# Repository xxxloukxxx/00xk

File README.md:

# Des keyboards qui vont presque bien :)

- [000k](https://github.com/xxxloukxxx/00xk/tree/main/000k) : Un 40%++, pas ergo, avec une ligne en plus inspiré
- [001k](https://github.com/xxxloukxxx/00xk/tree/main/001k) : Un ergo en 3x12+5, inspiré de revuing 41
- [002k](https://github.com/xxxloukxxx/00xk/tree/main/002k) : Un ergo en 3x12+6, inspiré de revuing 41 ... encore
- [003k](https://github.com/xxxloukxxx/00xk/tree/main/003k) : Un ergo en 4x12, inspiré de revuing 41 ... encore/encore
- [004k](https://github.com/xxxloukxxx/00xk/tree/main/004k) : Un ergo 52, inspiré de HillSide52

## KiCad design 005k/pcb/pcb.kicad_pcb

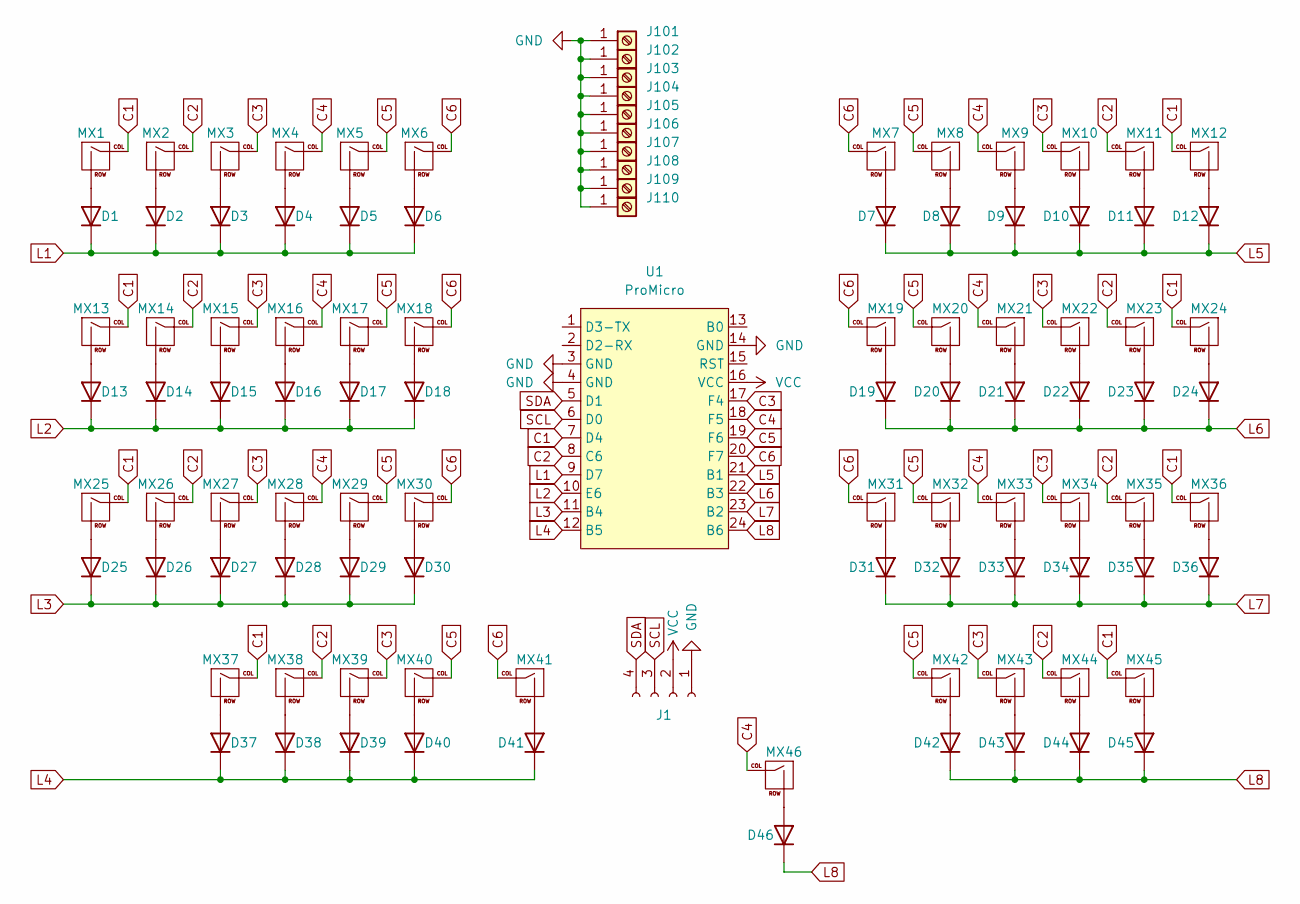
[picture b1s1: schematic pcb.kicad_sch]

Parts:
D1, D2, D3, D4, D5, D6, D7, D8, D9, D10, D11, D12, D13, D14, D15, D16, D17, D18, D19, D20, D21, D22, D23, D24, D25, D26, D27, D28, D29, D30, D31, D32, D33, D34, D35, D36, D37, D38, D39, D40, D41, D42, D43, D44, D45, D46: 1N4148; D_DO-35_SOD27_P7.62mm_Horizontal
J1: Conn_01x04_Socket; SSD1306-0.91-OLED-4pin-128x32
J101, J102, J103, J104, J105, J106, J107, J108, J109, J110: Screw_Terminal_01x01; MountingHole_2.2mm_M2
MX1, MX12, MX13, MX24, MX25, MX36, MX37, MX38, MX39, MX40, MX42: MX; MX-Alps-Hybrid-1.25U
MX2, MX3, MX4, MX5, MX6, MX7, MX8, MX9, MX10, MX11, MX14, MX15, MX16, MX17, MX18, MX19, MX20, MX21, MX22, MX23, MX26, MX27, MX28, MX29, MX30, MX31, MX32, MX33, MX34, MX35, MX43, MX44, MX45, MX46: MX; MX-Alps-Hybrid-1U
MX41: MX; MX-Alps-Hybrid-3U-ReversedStabilizers
U1: ProMicro; ProMicro_USBup

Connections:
C1: MX1.1 (COL), MX12.1 (COL), MX13.1 (COL), MX24.1 (COL), MX25.1 (COL), MX36.1 (COL), MX37.1 (COL), MX45.1 (COL), U1.7 (D4)
C2: MX2.1 (COL), MX11.1 (COL), MX14.1 (COL), MX23.1 (COL), MX26.1 (COL), MX35.1 (COL), MX38.1 (COL), MX44.1 (COL), U1.8 (C6)
C3: MX3.1 (COL), MX10.1 (COL), MX15.1 (COL), MX22.1 (COL), MX27.1 (COL), MX34.1 (COL), MX39.1 (COL), MX43.1 (COL), U1.17 (F4)
C4: MX4.1 (COL), MX9.1 (COL), MX16.1 (COL), MX21.1 (COL), MX28.1 (COL), MX33.1 (COL), MX46.1 (COL), U1.18 (F5)
C5: MX5.1 (COL), MX8.1 (COL), MX17.1 (COL), MX20.1 (COL), MX29.1 (COL), MX32.1 (COL), MX40.1 (COL), MX42.1 (COL), U1.19 (F6)
C6: MX6.1 (COL), MX7.1 (COL), MX18.1 (COL), MX19.1 (COL), MX30.1 (COL), MX31.1 (COL), MX41.1 (COL), U1.20 (F7)
GND: J1.1, J101.1, J102.1, J103.1, J104.1, J105.1, J106.1, J107.1, J108.1, J109.1, J110.1, U1.3 (GND), U1.4 (GND), U1.14 (GND)
L1: D1.1 (K), D2.1 (K), D3.1 (K), D4.1 (K), D5.1 (K), D6.1 (K), U1.9 (D7)
L2: D13.1 (K), D14.1 (K), D15.1 (K), D16.1 (K), D17.1 (K), D18.1 (K), U1.10 (E6)
L3: D25.1 (K), D26.1 (K), D27.1 (K), D28.1 (K), D29.1 (K), D30.1 (K), U1.11 (B4)
L4: D37.1 (K), D38.1 (K), D39.1 (K), D40.1 (K), D41.1 (K), U1.12 (B5)
L5: D7.1 (K), D8.1 (K), D9.1 (K), D10.1 (K), D11.1 (K), D12.1 (K), U1.21 (B1)
L6: D19.1 (K), D20.1 (K), D21.1 (K), D22.1 (K), D23.1 (K), D24.1 (K), U1.22 (B3)
L7: D31.1 (K), D32.1 (K), D33.1 (K), D34.1 (K), D35.1 (K), D36.1 (K), U1.23 (B2)
L8: D42.1 (K), D43.1 (K), D44.1 (K), D45.1 (K), D46.1 (K), U1.24 (B6)
unnamed: D1.2 (A), MX1.2 (ROW)
unnamed: D2.2 (A), MX2.2 (ROW)
unnamed: D3.2 (A), MX3.2 (ROW)
unnamed: D4.2 (A), MX4.2 (ROW)
unnamed: D5.2 (A), MX5.2 (ROW)
unnamed: D6.2 (A), MX6.2 (ROW)
unnamed: D7.2 (A), MX7.2 (ROW)
unnamed: D8.2 (A), MX8.2 (ROW)
unnamed: D9.2 (A), MX9.2 (ROW)
unnamed: D10.2 (A), MX10.2 (ROW)
unnamed: D11.2 (A), MX11.2 (ROW)
unnamed: D12.2 (A), MX12.2 (ROW)
unnamed: D13.2 (A), MX13.2 (ROW)
unnamed: D14.2 (A), MX14.2 (ROW)
unnamed: D15.2 (A), MX15.2 (ROW)
unnamed: D16.2 (A), MX16.2 (ROW)
unnamed: D17.2 (A), MX17.2 (ROW)
unnamed: D18.2 (A), MX18.2 (ROW)
unnamed: D19.2 (A), MX19.2 (ROW)
unnamed: D20.2 (A), MX20.2 (ROW)
unnamed: D21.2 (A), MX21.2 (ROW)
unnamed: D22.2 (A), MX22.2 (ROW)
unnamed: D23.2 (A), MX23.2 (ROW)
unnamed: D24.2 (A), MX24.2 (ROW)
unnamed: D25.2 (A), MX25.2 (ROW)
unnamed: D26.2 (A), MX26.2 (ROW)
unnamed: D27.2 (A), MX27.2 (ROW)
unnamed: D28.2 (A), MX28.2 (ROW)
unnamed: D29.2 (A), MX29.2 (ROW)
unnamed: D30.2 (A), MX30.2 (ROW)
unnamed: D31.2 (A), MX31.2 (ROW)
unnamed: D32.2 (A), MX32.2 (ROW)
unnamed: D33.2 (A), MX33.2 (ROW)
unnamed: D34.2 (A), MX34.2 (ROW)
unnamed: D35.2 (A), MX35.2 (ROW)
unnamed: D36.2 (A), MX36.2 (ROW)
unnamed: D37.2 (A), MX37.2 (ROW)
unnamed: D38.2 (A), MX38.2 (ROW)
unnamed: D39.2 (A), MX39.2 (ROW)
unnamed: D40.2 (A), MX40.2 (ROW)
unnamed: D41.2 (A), MX41.2 (ROW)
unnamed: D42.2 (A), MX42.2 (ROW)
unnamed: D43.2 (A), MX43.2 (ROW)
unnamed: D44.2 (A), MX44.2 (ROW)
unnamed: D45.2 (A), MX45.2 (ROW)
unnamed: D46.2 (A), MX46.2 (ROW)
SCL: J1.3, U1.6 (D0)
SDA: J1.4, U1.5 (D1)
VCC: J1.2, U1.16 (VCC)

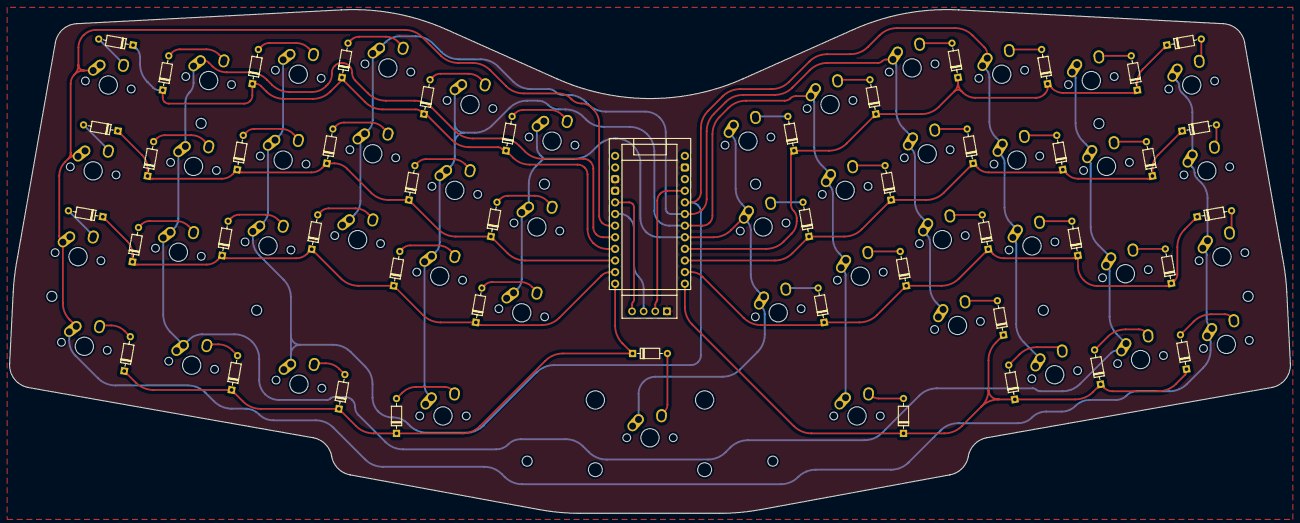
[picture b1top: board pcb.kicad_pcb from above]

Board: 2 copper layers, 279.9 x 110.1 mm, 104 parts (0 on the bottom side), 64 nets.

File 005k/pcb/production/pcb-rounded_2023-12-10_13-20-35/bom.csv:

Designator,Footprint,Quantity,Value,LCSC Part #
"D1, D10, D11, D12, D13, D14, D15, D16, D17, D18, D19, D2, D20, D21, D22, D23, D24, D25, D26, D27, D28, D29, D3, D30, D31, D32, D33, D34, D35, D36, D37, D38, D39, D4, D40, D41, D42, D43, D44, D45, D46, D47, D5, D6, D7, D8, D9",D_DO-35_SOD27_P7.62mm_Horizontal,47,1N4148,
J1,SSD1306-0.91-OLED-4pin-128x32,1,Screw_Terminal_01x04,
"MX1, MX10, MX11, MX12, MX13, MX14, MX15, MX16, MX17, MX18, MX19, MX2, MX20, MX21, MX22, MX23, MX24, MX25, MX26, MX27, MX28, MX29, MX3, MX30, MX31, MX32, MX33, MX34, MX35, MX36, MX37, MX38, MX39, MX4, MX40, MX41, MX42, MX43, MX44, MX45, MX46, MX47, MX5, MX6, MX7, MX8, MX9",MX-Alps-Hybrid-1U,47,MX,

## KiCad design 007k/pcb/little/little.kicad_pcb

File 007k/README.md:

# 007k

Pour Gigi ... Exploded One

## Little

... et pourquoi pas avec un OLED ?

## Big

à voir car pas de place pour le Promicro

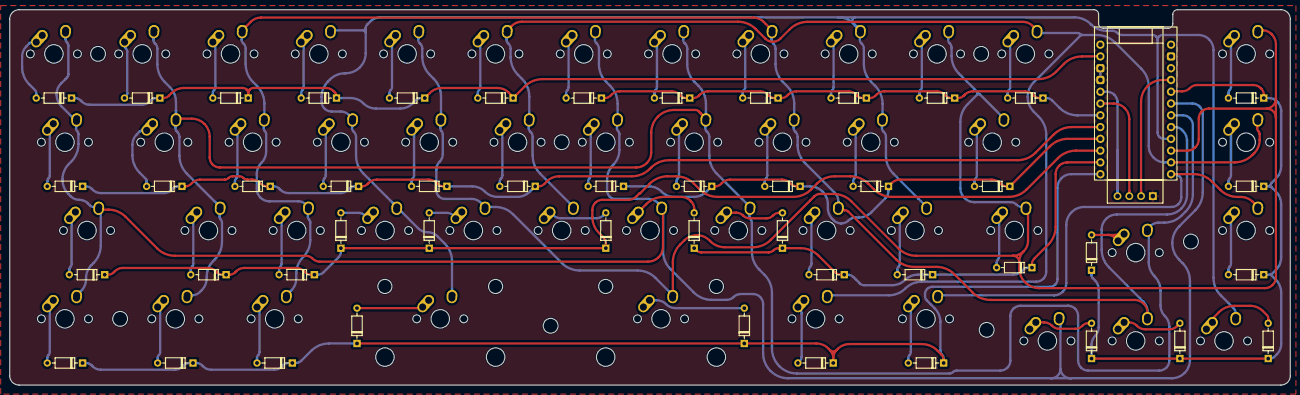
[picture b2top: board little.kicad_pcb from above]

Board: 2 copper layers, 276.2 x 81.0 mm, 105 parts (0 on the bottom side), 67 nets.

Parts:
D1, D2, D3, D4, D5, D6, D7, D8, D9, D10, D11, D12, D13, D14, D15, D16, D17, D18, D19, D20, D21, D22, D23, D24, D25, D26, D27, D28, D29, D30, D31, D32, D33, D34, D35, D36, D37, D38, D39, D40, D41, D42, D43, D44, D45, D46, D47, D48: 1N4148; D_DO-35_SOD27_P7.62mm_Horizontal
MX1, MX2, MX3, MX4, MX5, MX6, MX7, MX8, MX9, MX10, MX11, MX12, MX14, MX15, MX16, MX17, MX18, MX19, MX20, MX21, MX22, MX25, MX26, MX27, MX28, MX29, MX30, MX31, MX32, MX33, MX37, MX42, MX43, MX44, MX45, MX46, MX47, MX48: MX_SW_solder; MX-Alps-Hybrid-1U
MX13, MX34, MX35, MX36, MX40, MX41: MX_SW_solder; MX-Alps-Hybrid-1.25U
MX23, MX24: MX_SW_solder; MX-Alps-Hybrid-1.75U
MX38: MX_SW_solder; MX-Alps-Hybrid-2.75U
MX39: MX_SW_solder; MX-Alps-Hybrid-2.25U
OLED1: Conn_01x04_Socket; SSD1306-0.91-OLED-4pin-128x32
REF1, REF2, REF3, REF4, REF5, REF6, REF7: MountingHole_3.2mm_M3
U1: ProMicro; ProMicro_USBup

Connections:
COL1: MX1.2, MX7.2, MX13.2, MX19.2, MX24.2, MX30.2, MX35.2, MX42.2, U1.18 (F5)
COL2: MX2.2, MX8.2, MX14.2, MX20.2, MX25.2, MX31.2, MX36.2, MX43.2, U1.19 (F6)
COL3: MX3.2, MX9.2, MX15.2, MX21.2, MX26.2, MX32.2, MX37.2, MX44.2, U1.20 (F7)
COL4: MX4.2, MX10.2, MX16.2, MX22.2, MX27.2, MX33.2, MX38.2, MX45.2, U1.21 (B1)
COL5: MX5.2, MX11.2, MX17.2, MX23.2, MX28.2, MX34.2, MX39.2, MX46.2, U1.22 (B3)
COL6: MX6.2, MX12.2, MX18.2, MX29.2, MX40.2, MX47.2, U1.23 (B2)
COL7: MX41.2, MX48.2, U1.24 (B6)
GND: OLED1.1, U1.3 (GND), U1.4 (GND), U1.14 (GND)
L1: D1.1 (K), D2.1 (K), D3.1 (K), D4.1 (K), D5.1 (K), D6.1 (K), U1.2 (D2-RX)
L2: D7.1 (K), D8.1 (K), D9.1 (K), D10.1 (K), D11.1 (K), D12.1 (K), U1.7 (D4)
L3: D13.1 (K), D14.1 (K), D15.1 (K), D16.1 (K), D17.1 (K), D18.1 (K), U1.8 (C6)
L4: D19.1 (K), D20.1 (K), D21.1 (K), D22.1 (K), D23.1 (K), U1.9 (D7)
L5: D24.1 (K), D25.1 (K), D26.1 (K), D27.1 (K), D28.1 (K), D29.1 (K), U1.10 (E6)
L6: D30.1 (K), D31.1 (K), D32.1 (K), D33.1 (K), D34.1 (K), U1.11 (B4)
L7: D35.1 (K), D36.1 (K), D37.1 (K), D38.1 (K), D39.1 (K), D40.1 (K), D41.1 (K), U1.12 (B5)
L8: D42.1 (K), D43.1 (K), D44.1 (K), D45.1 (K), D46.1 (K), D47.1 (K), D48.1 (K), U1.17 (F4)
unnamed: D1.2 (A), MX1.1
unnamed: D2.2 (A), MX2.1
unnamed: D3.2 (A), MX3.1
unnamed: D4.2 (A), MX4.1
unnamed: D5.2 (A), MX5.1
unnamed: D6.2 (A), MX6.1
unnamed: D7.2 (A), MX7.1
unnamed: D8.2 (A), MX8.1
unnamed: D9.2 (A), MX9.1
unnamed: D10.2 (A), MX10.1
unnamed: D11.2 (A), MX11.1
unnamed: D12.2 (A), MX12.1
unnamed: D13.2 (A), MX13.1
unnamed: D14.2 (A), MX14.1
unnamed: D15.2 (A), MX15.1
unnamed: D16.2 (A), MX16.1
unnamed: D17.2 (A), MX17.1
unnamed: D18.2 (A), MX18.1
unnamed: D19.2 (A), MX19.1
unnamed: D20.2 (A), MX20.1
unnamed: D21.2 (A), MX21.1
unnamed: D22.2 (A), MX22.1
unnamed: D23.2 (A), MX23.1
unnamed: D24.2 (A), MX24.1
unnamed: D25.2 (A), MX25.1
unnamed: D26.2 (A), MX26.1
unnamed: D27.2 (A), MX27.1
unnamed: D28.2 (A), MX28.1
unnamed: D29.2 (A), MX29.1
unnamed: D30.2 (A), MX30.1
unnamed: D31.2 (A), MX31.1
unnamed: D32.2 (A), MX32.1
unnamed: D33.2 (A), MX33.1
unnamed: D34.2 (A), MX34.1
unnamed: D35.2 (A), MX35.1
unnamed: D36.2 (A), MX36.1
unnamed: D37.2 (A), MX37.1
unnamed: D38.2 (A), MX38.1
unnamed: D39.2 (A), MX39.1
unnamed: D40.2 (A), MX40.1
unnamed: D41.2 (A), MX41.1
unnamed: D42.2 (A), MX42.1
unnamed: D43.2 (A), MX43.1
unnamed: D44.2 (A), MX44.1
unnamed: D45.2 (A), MX45.1
unnamed: D46.2 (A), MX46.1
unnamed: D47.2 (A), MX47.1
unnamed: D48.2 (A), MX48.1
SCL: OLED1.3, U1.6 (D0)
SDA: OLED1.4, U1.5 (D1)
VCC: OLED1.2, U1.16 (VCC)

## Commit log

2023-12-02 sam. 02 déc. 2023 16:25:14 CET
2023-12-02 sam. 02 déc. 2023 20:31:41 CET
2023-12-02 sam. 02 déc. 2023 20:41:54 CET
2023-12-02 sam. 02 déc. 2023 22:48:49 CET
2023-12-03 dim. 03 déc. 2023 16:12:46 CET
2023-12-03 dim. 03 déc. 2023 16:20:19 CET
2023-12-03 dim. 03 déc. 2023 16:43:29 CET
2023-12-04 lun. 04 déc. 2023 22:35:32 CET
2023-12-05 mar. 05 déc. 2023 23:57:22 CET
2023-12-06 mer. 06 déc. 2023 23:16:58 CET
2023-12-07 jeu. 07 déc. 2023 07:05:12 CET
2023-12-10 dim. 10 déc. 2023 12:03:13 CET
2023-12-10 dim. 10 déc. 2023 13:12:07 CET
2023-12-10 dim. 10 déc. 2023 20:23:19 CET
2023-12-16 sam. 16 déc. 2023 22:31:26 CET
2023-12-18 lun. 18 déc. 2023 07:38:35 CET
2023-12-18 lun. 18 déc. 2023 09:13:05 CET
2023-12-18 lun. 18 déc. 2023 09:21:16 CET
2023-12-19 mar. 19 déc. 2023 22:16:39 CET
2023-12-21 jeu. 21 déc. 2023 06:59:11 CET
2023-12-21 jeu. 21 déc. 2023 09:29:24 CET
2023-12-21 jeu. 21 déc. 2023 12:06:00 CET
2023-12-22 ven. 22 déc. 2023 01:02:29 CET
2023-12-22 ven. 22 déc. 2023 11:54:46 CET
2023-12-22 ven. 22 déc. 2023 21:50:38 CET
2023-12-23 sam. 23 déc. 2023 09:52:10 CET
2023-12-23 sam. 23 déc. 2023 15:06:00 CET
2023-12-23 sam. 23 déc. 2023 20:08:59 CET
2023-12-25 lun. 25 déc. 2023 13:50:01 CET
2023-12-25 lun. 25 déc. 2023 14:32:07 CET
2023-12-25 lun. 25 déc. 2023 14:50:21 CET
2023-12-28 jeu. 28 déc. 2023 20:04:29 CET
2023-12-28 jeu. 28 déc. 2023 23:03:25 CET
2023-12-29 ven. 29 déc. 2023 11:31:16 CET
2023-12-29 ven. 29 déc. 2023 20:25:38 CET
2023-12-29 ven. 29 déc. 2023 20:30:05 CET
2024-01-02 mar. 02 janv. 2024 15:40:53 CET
2024-01-03 mer. 03 janv. 2024 12:07:08 CET
2024-01-04 jeu. 04 janv. 2024 14:54:00 CET
2024-01-06 sam. 06 janv. 2024 11:30:38 CET
2024-01-06 sam. 06 janv. 2024 12:07:38 CET
2024-01-06 sam. 06 janv. 2024 15:39:42 CET
2024-01-07 dim. 07 janv. 2024 17:36:37 CET
